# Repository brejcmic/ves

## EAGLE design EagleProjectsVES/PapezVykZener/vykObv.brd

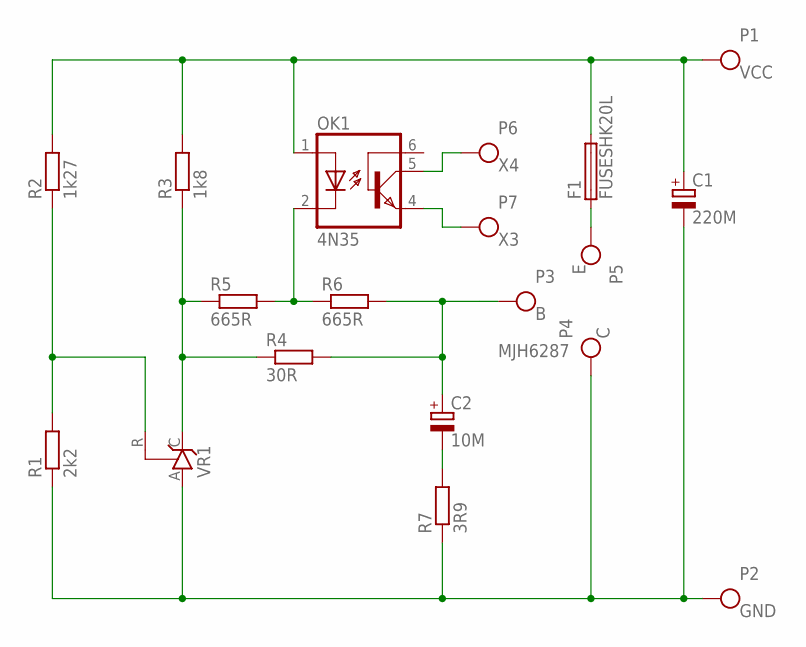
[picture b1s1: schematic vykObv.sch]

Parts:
C1: 220M; E3,5-8
C2: 10M; E22-6
F1: FUSESHK20L; SHK20L
OK1: 4N35; DIL06
P1: VCC; PAD2.5MM
P2: GND; PAD2.5MM
P3: B; PAD2.5MM
P4: C; PAD2.5MM
P5: E; PAD2.5MM
P6: X4; PAD1.6MM
P7: X3; PAD1.6MM
R1: 2k2; 0207/10
R2: 1k27; 0207/10
R3: 1k8; 0207/10
R4: 30R; 0207/10
R5, R6: 665R; 0207/10
R7: 3R9; 0207/10
VR1: TL431CLP; TO92-CLP

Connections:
EMIT: F1.1A (1), F1.1B (1), P5.P$1
GND: C1.-, P2.P$1, P4.P$1, R1.1, R7.1, VR1.A
unnamed: OK1.2 (C), R5.2, R6.1
unnamed: C2.+, P3.P$1, R4.2, R6.2
unnamed: R3.1, R4.1, R5.1, VR1.C
unnamed: OK1.4 (EMI), P7.P$1
unnamed: OK1.5 (COL), P6.P$1
unnamed: R1.2, R2.1, VR1.R
unnamed: C2.-, R7.2
VDD: C1.+, F1.2A (2), F1.2B (2), OK1.1 (A), P1.P$1, R2.2, R3.2

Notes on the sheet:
MJH6287

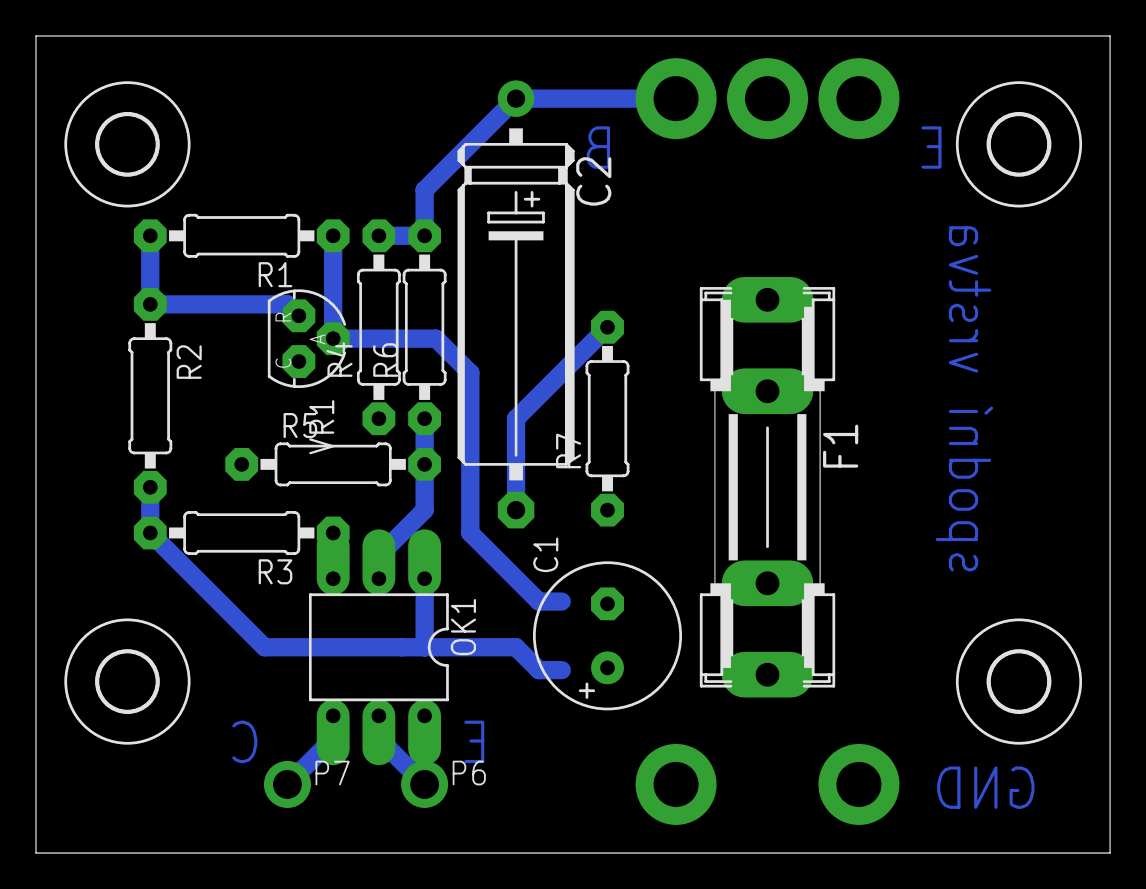
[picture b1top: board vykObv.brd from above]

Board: 2 copper layers, 59.7 x 45.4 mm, 23 parts (0 on the bottom side), 10 nets.

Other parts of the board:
U$1, U$2, U$3, U$4: 3,2

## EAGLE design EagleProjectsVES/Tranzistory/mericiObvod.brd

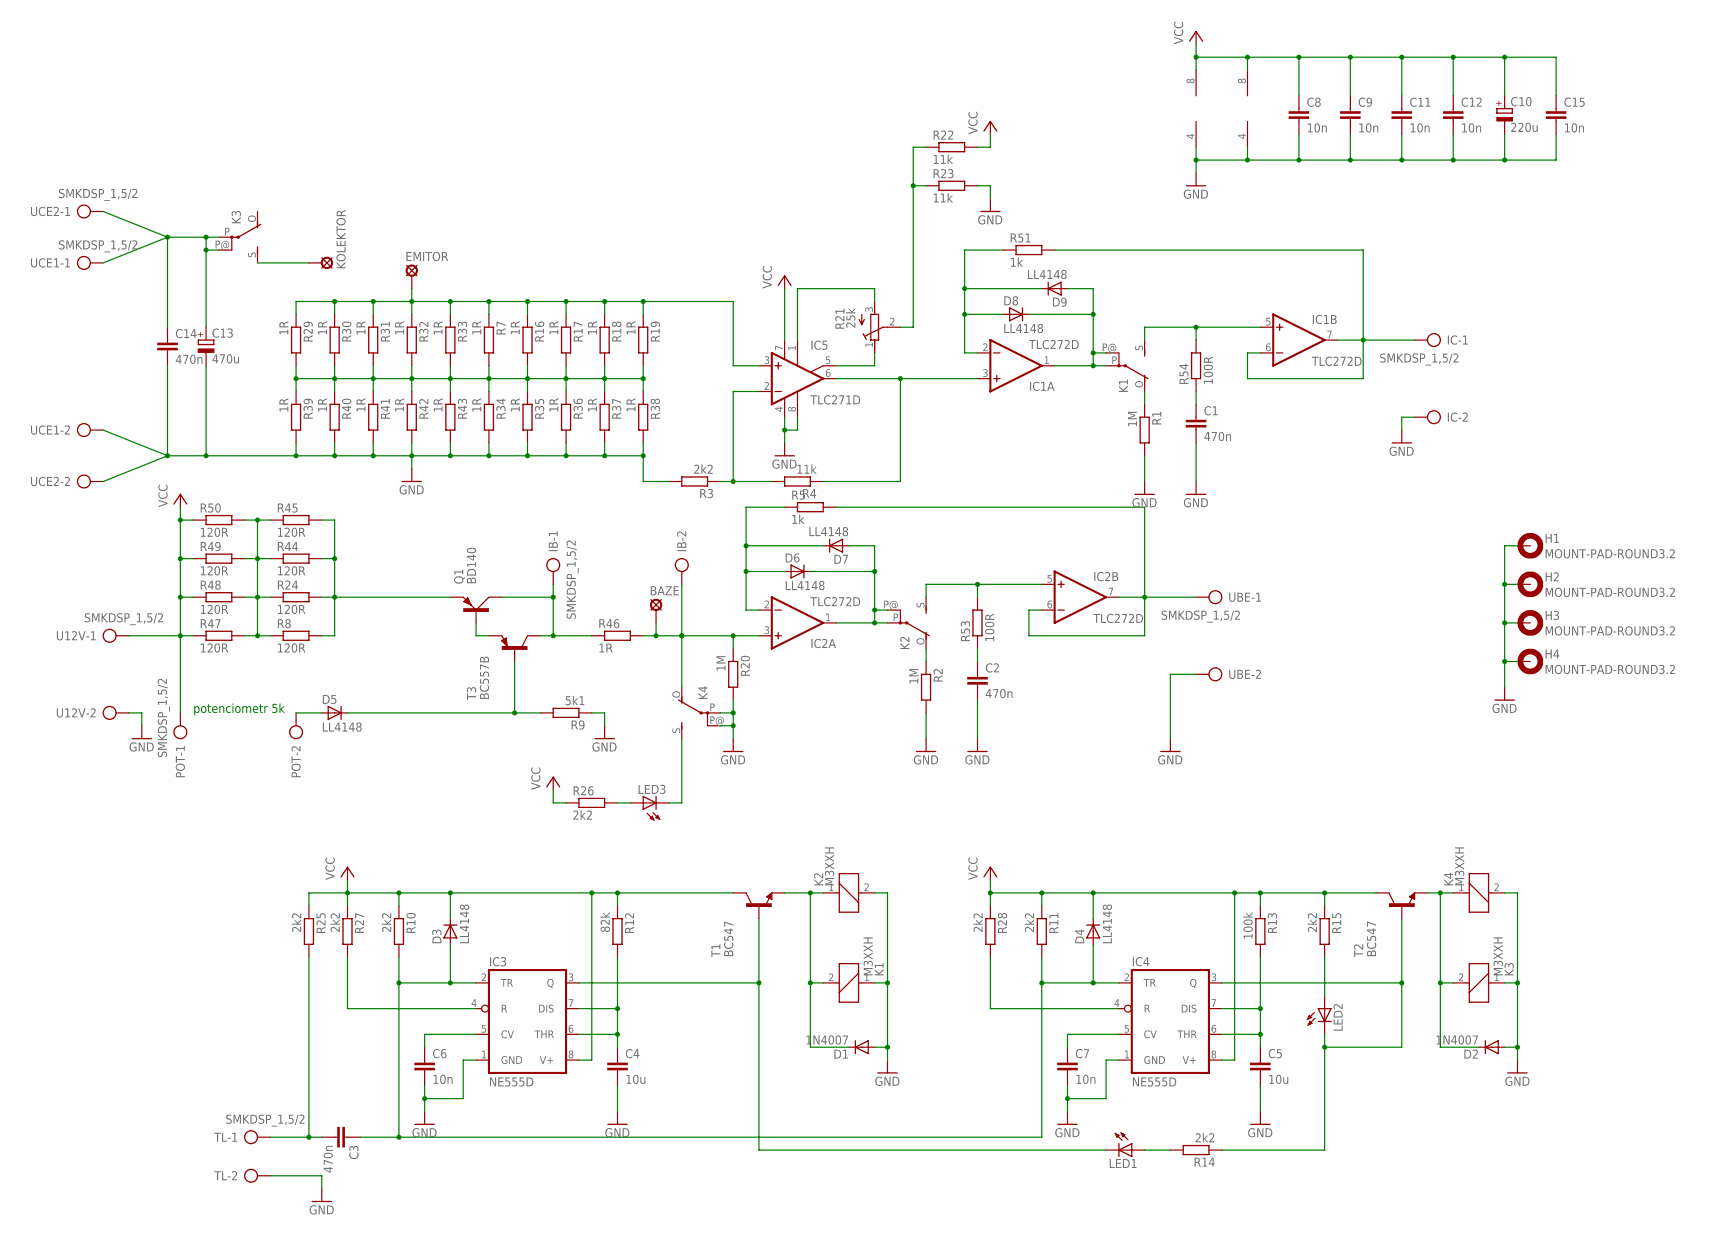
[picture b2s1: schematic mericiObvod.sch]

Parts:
BAZE: SE13
C1, C2, C3: 470n; C0805K
C4, C5: 10u; C0805K
C6, C7, C8, C9, C11, C12, C15: 10n; C0805K
C10: 220u; E5-8,5
C13: 470u; E5-8,5
C14: 470n; C050-030X075
D1, D2: 1N4007; DO41-10
D3, D4, D5, D6, D7, D8, D9: LL4148; SOD80
EMITOR: SE13
H1, H2, H3, H4: MOUNT-PAD-ROUND3.2; 3,2-PAD
IB: SMKDSP_1,5/2
IC: SMKDSP_1,5/2
IC1, IC2: TLC272D; SO08
IC3, IC4: NE555D; SO08
IC5: TLC271D; SO08
K1, K2, K3, K4: M3XXH
KOLEKTOR: SE13
LED1, LED2, LED3: LED3MM
POT: SMKDSP_1,5/2
Q1: BD140; TO126AV
R1, R2, R20: 1M; R0805
R3, R10, R11, R14, R15, R25, R26, R27, R28: 2k2; R0805
R4, R22, R23: 11k; R0805
R5, R51: 1k; R0805
R7, R16, R17, R18, R19, R29, R30, R31, R32, R33, R34, R35, R36, R37, R38, R39, R40, R41, R42, R43, R46: 1R; R0805
R8, R24, R44, R45, R47, R48, R49, R50: 120R; R0805
R9: 5k1; R0805
R12: 82k; R0805
R13: 100k; R0805
R21: 25k; RTRIMT18
R53, R54: 100R; R0805
T1, T2: BC547; TO92-CBE
T3: BC557B; TO92-EBC
TL: SMKDSP_1,5/2
U12V: SMKDSP_1,5/2
UBE: SMKDSP_1,5/2
UCE1, UCE2: SMKDSP_1,5/2

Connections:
GND: C1.2, C2.2, C4.2, C5.2, C6.2, C7.2, C8.2, C9.2, C10.-, C11.2, C12.2, C13.-, C14.2, C15.2, D1.A, D2.A, H1.B3,2, H2.B3,2, H3.B3,2, H4.B3,2, IC.2, IC1.4 (V-), IC2.4 (V-), IC3.1 (GND), IC4.1 (GND), IC5.4 (V-), IC5.8 (OPT), K1.1, K2.2, K3.1, K4.2, K4.P, K4.P@, R1.2, R2.2, R3.2, R9.1, R20.2, R23.2, R34.2, R35.2, R36.2, R37.2, R38.2, R39.2, R40.2, R41.2, R42.2, R43.2, TL.2, U12V.2, UBE.2, UCE1.2, UCE2.2
unnamed: IC5.2 (-IN), R3.1, R4.2
unnamed: IC2.6 (-IN), IC2.7 (OUT), R5.2, UBE.1
unnamed: C1.1, R54.1
unnamed: C2.1, R53.1
unnamed: D6.1 (C), D7.2 (A), IC2.1 (OUT), K2.P, K2.P@
unnamed: D8.1 (C), D9.2 (A), IC1.1 (OUT), K1.P, K1.P@
unnamed: K2.O, R2.1
unnamed: R7.2, R16.2, R17.2, R18.2, R19.2, R29.2, R30.2, R31.2, R32.2, R33.2, R34.1, R35.1, R36.1, R37.1, R38.1, R39.1, R40.1, R41.1, R42.1, R43.1
unnamed: Q1.B, T3.E
unnamed: IC.1, IC1.6 (-IN), IC1.7 (OUT), R51.2
unnamed: D6.2 (A), D7.1 (C), IC2.2 (-IN), R5.1
unnamed: R8.1, R24.1, R44.1, R45.1, R47.2, R48.2, R49.2, R50.2
unnamed: BAZE.MP, IB.2, IC2.3 (+IN), K4.O, R20.1, R46.2
unnamed: D5.2 (A), POT.2
unnamed: D5.1 (C), R9.2, T3.B
unnamed: IB.1, Q1.C, R46.1, T3.C
unnamed: Q1.E, R8.2, R24.2, R44.2, R45.2
unnamed: D1.C, K1.2, K2.1, T1.E
unnamed: IC3.3 (Q), LED1.K (C), T1.B
unnamed: IC4.3 (Q), LED2.K (C), R14.1, T2.B
unnamed: D2.C, K3.2, K4.1, T2.E
unnamed: C3.1, D3.2 (A), D4.2 (A), IC3.2 (TR), IC4.2 (TR), R10.2, R11.2
unnamed: LED1.A, R14.2
unnamed: C5.1, IC4.6 (THR), IC4.7 (DIS), R13.2
unnamed: C4.1, IC3.6 (THR), IC3.7 (DIS), R12.2
unnamed: C6.1, IC3.5 (CV)
unnamed: IC1.3 (+IN), IC5.6 (OUT), R4.1
unnamed: C7.1, IC4.5 (CV)
unnamed: LED2.A, R15.2
unnamed: C3.2, R25.2, TL.1
unnamed: LED3.A, R26.2
unnamed: IC5.5 (ON2), R21.1 (E)
unnamed: IC5.1 (ON1), R21.3 (A)
unnamed: R21.2 (S), R22.1, R23.1
unnamed: K4.S, LED3.K (C)
unnamed: IC3.4 (R), R27.2
unnamed: IC4.4 (R), R28.2
unnamed: K1.O, R1.1
unnamed: D8.2 (A), D9.1 (C), IC1.2 (-IN), R51.1
unnamed: C13.+, C14.1, K3.P, K3.P@, UCE1.1, UCE2.1
unnamed: IC1.5 (+IN), K1.S, R54.2
unnamed: IC2.5 (+IN), K2.S, R53.2
unnamed: EMITOR.MP, IC5.3 (+IN), R7.1, R16.1, R17.1, R18.1, R19.1, R29.1, R30.1, R31.1, R32.1, R33.1
unnamed: K3.S, KOLEKTOR.MP
VCC: C8.1, C9.1, C10.+, C11.1, C12.1, C15.1, D3.1 (C), D4.1 (C), IC1.8 (V+), IC2.8 (V+), IC3.8 (V+), IC4.8 (V+), IC5.7 (V+), POT.1, R10.1, R11.1, R12.1, R13.1, R15.1, R22.2, R25.1, R26.1, R27.1, R28.1, R47.1, R48.1, R49.1, R50.1, T1.C, T2.C, U12V.1

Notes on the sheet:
potenciometr 5k

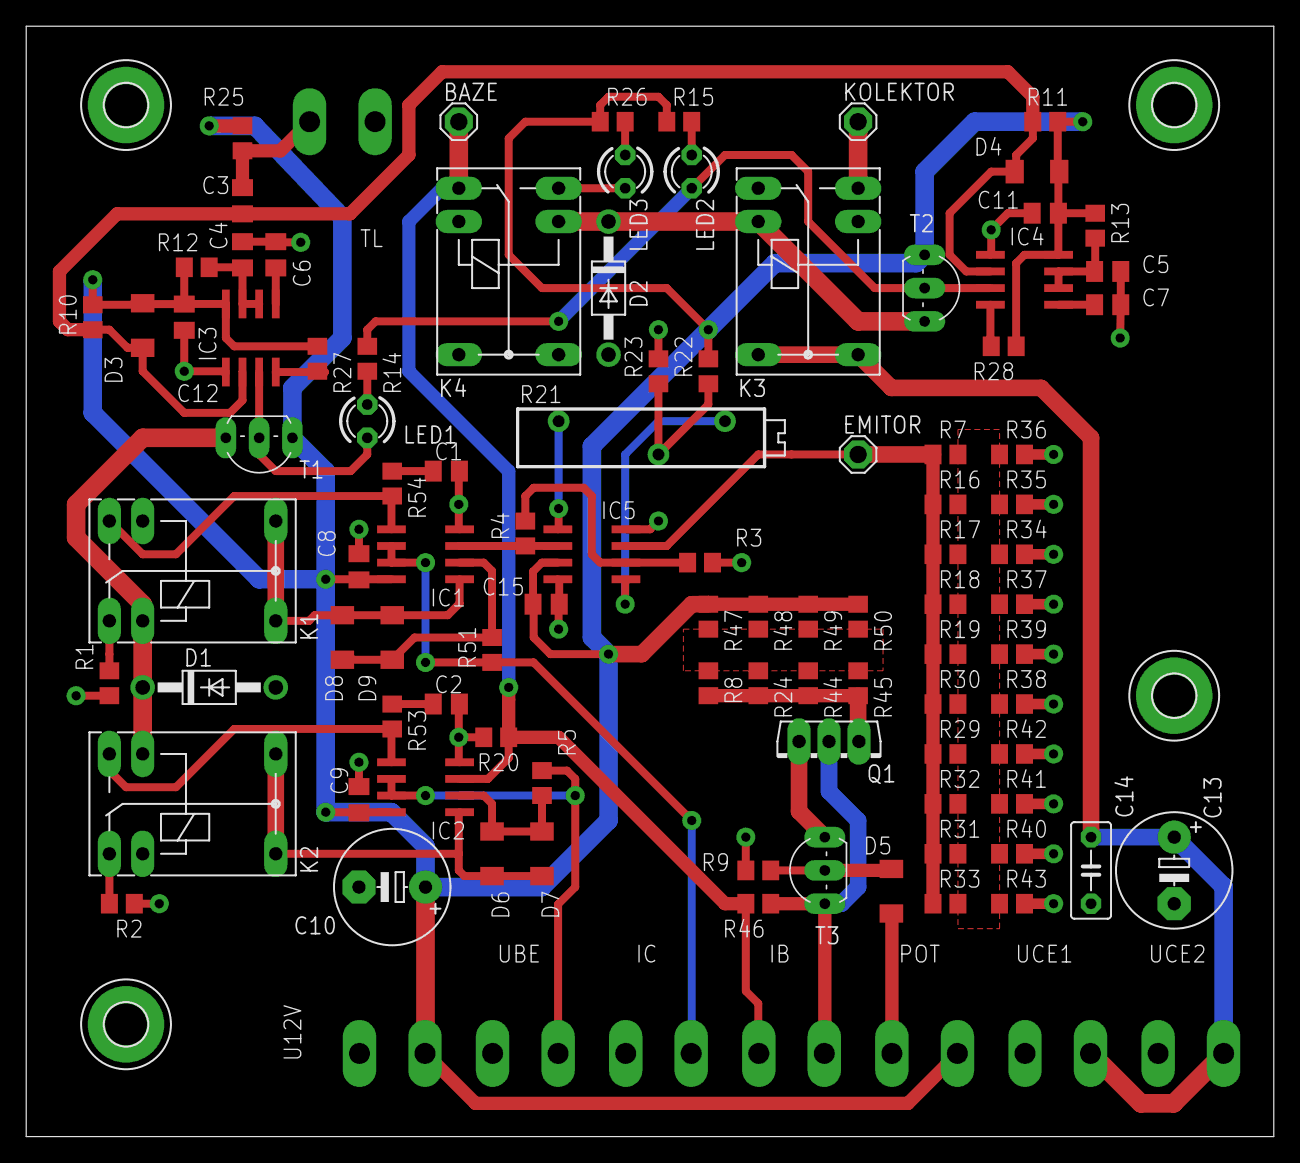
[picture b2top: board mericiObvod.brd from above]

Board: 2 copper layers, 95.2 x 84.8 mm, 107 parts (0 on the bottom side), 46 nets.

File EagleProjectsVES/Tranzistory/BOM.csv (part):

Partlist exported from C:/Users/brejcmic/GITs/ves/EagleProjectsVES/Tranzistory/mericiObvod.sch at 19.9.2017 11:37:58

Qty Value              Device              Package      Parts                                                                                                  Description                                                               MF      MPN     OC_FARNELL OC_NEWARK
2                      BC547B-NPN-TO92-CBE TO92-CBE     T1, T2                                                                                                 NPN Transistror                                                                                               
3                      LED3MM              LED3MM       LED1, LED2, LED3                                                                                       LED                                                                                                           
2   100R               R-EU_R0805          R0805        R53, R54                                                                                               RESISTOR, European symbol                                                                                     
1   100k               R-EU_R0805          R0805        R13                                                                                                    RESISTOR, European symbol                                                                                     
7   10n                C-EUC0805K          C0805K       C6, C7, C8, C9, C11, C12, C15                                                                          CAPACITOR, European symbol                                                                                    
2   10u                C-EUC0805K          C0805K       C4, C5                                                                                                 CAPACITOR, European symbol                                                                                    
3   11k                R-EU_R0805          R0805        R4, R22, R23                                                                                           RESISTOR, European symbol                                                                                     
8   120R               R-EU_R0805          R0805        R8, R24, R44, R45, R47, R48, R49, R50                                                                  RESISTOR, European symbol                                                                                     
3   1M                 R-EU_R0805          R0805        R1, R2, R20                                                                                            RESISTOR, European symbol                                                                                     
2   1N4007             DIODE-DO41-10       DO41-10      D1, D2                                                                                                 DIODE                                                                                                         
21  1R                 R-EU_R0805          R0805        R7, R16, R17, R18, R19, R29, R30, R31, R32, R33, R34, R35, R36, R37, R38, R39, R40, R41, R42, R43, R46 RESISTOR, European symbol                                                                                     
2   1k                 R-EU_R0805          R0805        R5, R51                                                                                                RESISTOR, European symbol                                                                                     
1   220u               CPOL-EUE5-8.5       E5-8,5       C10                                                                                                    POLARIZED CAPACITOR, European symbol                                                                          
1   25k                R-TRIMMT18          RTRIMT18     R21                                                                                                    Trimm resistor                                                                                                
9   2k2                R-EU_R0805          R0805        R3, R10, R11, R14, R15, R25, R26, R27, R28                                                             RESISTOR, European symbol                                                                                     
1   470n               C-EU050-030X075     C050-030X075 C14                                                                                                    CAPACITOR, European symbol                                                                                    
3   470n               C-EUC0805K          C0805K       C1, C2, C3                                                                                             CAPACITOR, European symbol                                                                                    
1   470u               CPOL-EUE5-8.5       E5-8,5       C13                                                                                                    POLARIZED CAPACITOR, European symbol                                                                          
1   5k1                R-EU_R0805          R0805        R9                                                                                                     RESISTOR, European symbol                                                                                     
1   82k                R-EU_R0805          R0805        R12                                                                                                    RESISTOR, European symbol                                                                                     
1   BC557B             BC557B              TO92-EBC     T3                                                                                                     PNP Transistror                                                                                               
1   BD140              BD140               TO126AV      Q1                                                                                                     PNP TRANSISTOR                                                                                                
7   LL4148             D-SOD-80            SOD80        D3, D4, D5, D6, D7, D8, D9                                                                             DIODE                                                                                                         
4   M3XXH              M3XXH               M3XXH        K1, K2, K3, K4                                                                                         RELAY                                                                                     unknown    unknown  
4   MOUNT-PAD-ROUND3.2 MOUNT-PAD-ROUND3.2  3,2-PAD      H1, H2, H3, H4                                                                                         MOUNTING PAD, round                                                                                           
2   NE555D             NE555D              SO08         IC3, IC4                                                                                               TIMER                                                                                                         
3   SE13               SE13                SE13         BAZE, EMITOR, KOLEKTOR                                                                                 SOLDER PAD E1542,  drill 1,3mm, distributor Buerklin, 07F815                                                  
8   SMKDSP_1,5/2       SMKDSP_1,5/2        SMKDSP_1,5/2 IB, IC, POT, TL, U12V, UBE, UCE1, UCE2                                                                 Printklemme, Nennstrom: 17,5 A, Bemessungsspannung: 250 V, Raster: 5,0 mm FARNELL 1733570 3041244    69C8588  
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
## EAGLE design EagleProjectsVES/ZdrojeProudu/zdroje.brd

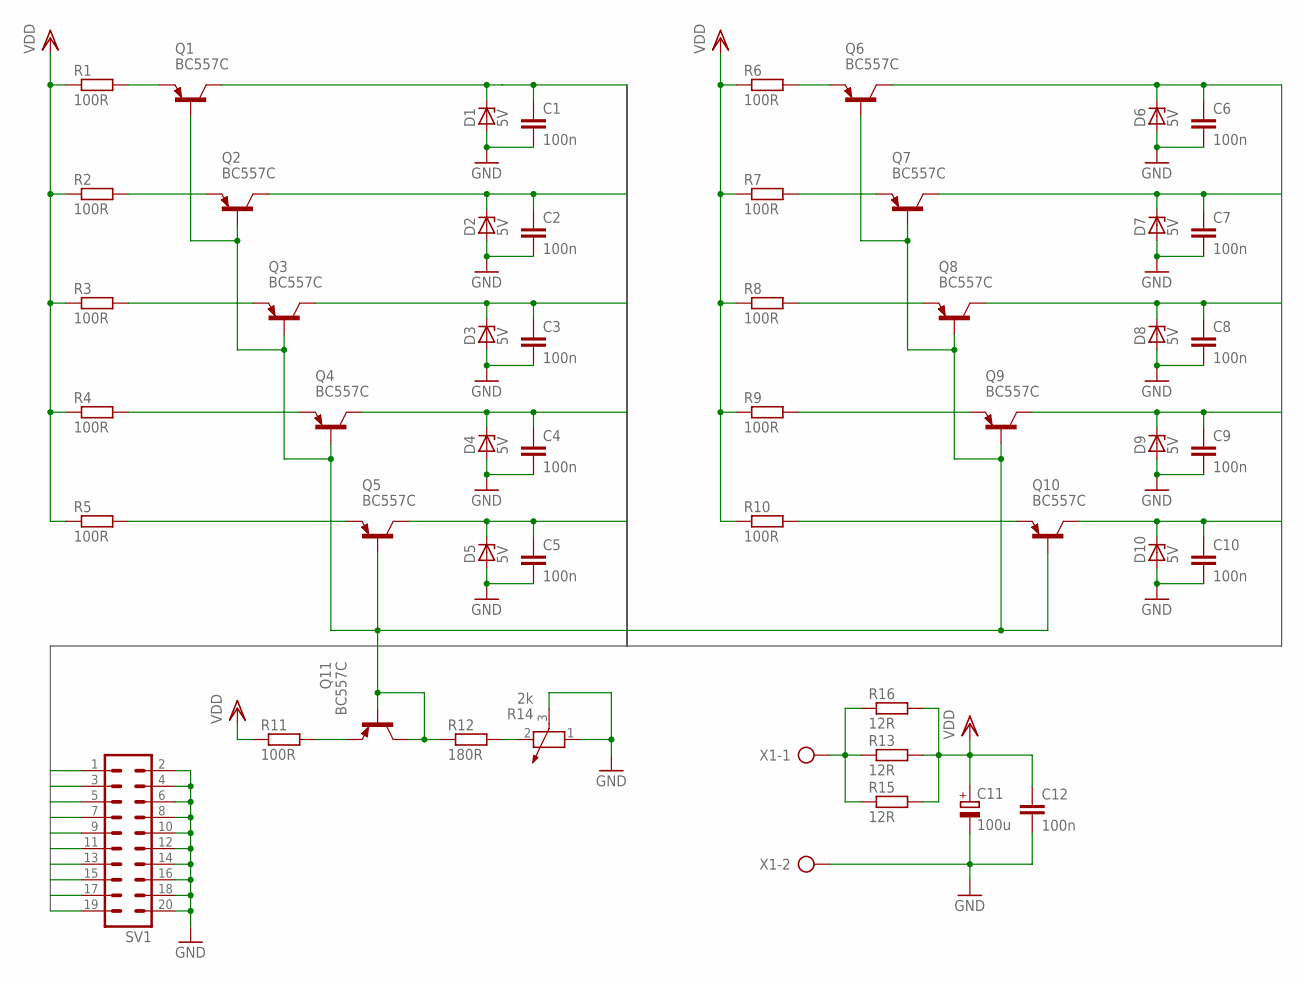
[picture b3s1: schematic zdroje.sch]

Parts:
C1, C2, C3, C4, C5, C6, C7, C8, C9, C10, C12: 100n; C050-030X075
C11: 100u; E5-8,5
D1, D2, D3, D4, D5, D6, D7, D8, D9, D10: 5V; DO35Z10
Q1, Q2, Q3, Q4, Q5, Q6, Q7, Q8, Q9, Q10, Q11: BC557C; TO92-EBC
R1, R2, R3, R4, R5, R6, R7, R8, R9, R10, R11: 100R; 0207/10
R12: 180R; 0207/10
R13, R15, R16: 12R; 0207/10
R14: 2k; PT-SPIN
SV1: MA10-2
X1: AK300/2

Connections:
GND: C1.2, C2.2, C3.2, C4.2, C5.2, C6.2, C7.2, C8.2, C9.2, C10.2, C11.-, C12.2, D1.A, D2.A, D3.A, D4.A, D5.A, D6.A, D7.A, D8.A, D9.A, D10.A, R14.1, R14.3, SV1.2, SV1.4, SV1.6, SV1.8, SV1.10, SV1.12, SV1.14, SV1.16, SV1.18, SV1.20, X1.2
I1: C1.1, D1.C, Q1.C, SV1.1
I2: C2.1, D2.C, Q2.C, SV1.3
I3: C3.1, D3.C, Q3.C, SV1.5
I4: C4.1, D4.C, Q4.C, SV1.7
I5: C5.1, D5.C, Q5.C, SV1.9
I6: C6.1, D6.C, Q6.C, SV1.11
I7: C7.1, D7.C, Q7.C, SV1.13
I8: C8.1, D8.C, Q8.C, SV1.15
I9: C9.1, D9.C, Q9.C, SV1.17
I10: C10.1, D10.C, Q10.C, SV1.19
unnamed: Q1.E, R1.2
unnamed: Q2.E, R2.2
unnamed: Q3.E, R3.2
unnamed: Q4.E, R4.2
unnamed: Q5.E, R5.2
unnamed: Q6.E, R6.2
unnamed: Q7.E, R7.2
unnamed: Q8.E, R8.2
unnamed: Q9.E, R9.2
unnamed: Q10.E, R10.2
unnamed: R12.2, R14.2
unnamed: Q1.B, Q2.B, Q3.B, Q4.B, Q5.B, Q6.B, Q7.B, Q8.B, Q9.B, Q10.B, Q11.B, Q11.C, R12.1
unnamed: Q11.E, R11.2
unnamed: R13.1, R15.1, R16.1, X1.1
VDD: C11.+, C12.1, R1.1, R2.1, R3.1, R4.1, R5.1, R6.1, R7.1, R8.1, R9.1, R10.1, R11.1, R13.2, R15.2, R16.2

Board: 2 copper layers, 51 parts (0 on the bottom side), 26 nets, no tracks yet.

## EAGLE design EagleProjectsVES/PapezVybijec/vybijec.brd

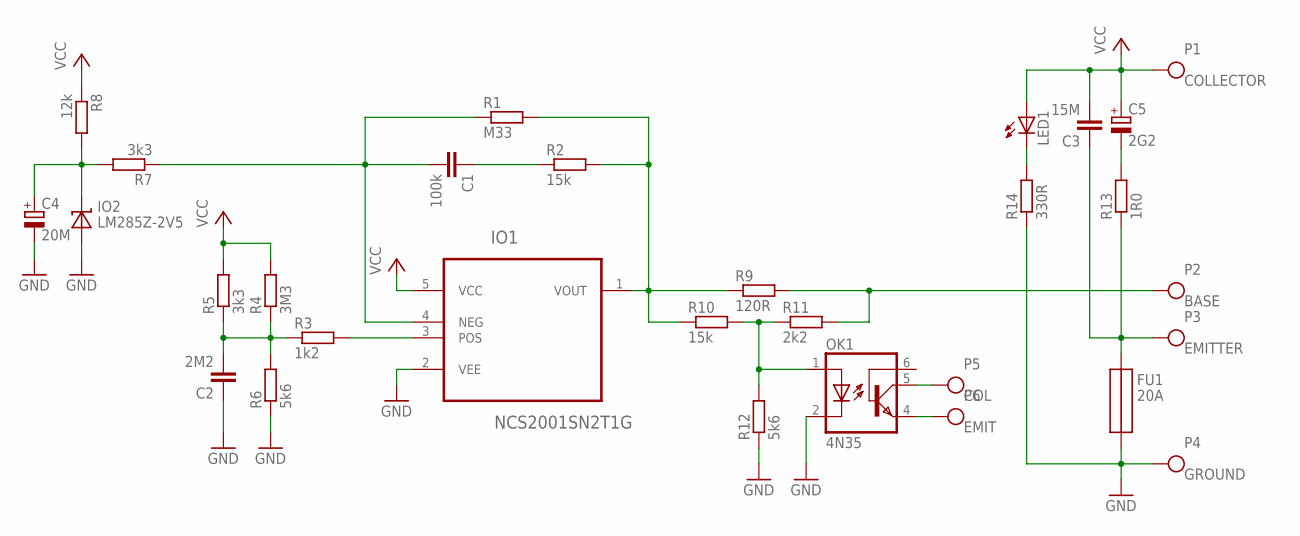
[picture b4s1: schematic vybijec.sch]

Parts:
C1: 100k; C050-025X075
C2: 2M2; C050-050X075
C3: 15M; C050-075X075
C4: 20M; E22-6
C5: 2G2; E5-10,5
FU1: 20A; POJ20X6
IO1: NCS2001SN2T1G; SOT95P275X110-5N
IO2: LM285Z-2V5; TO92-
LED1: LED3MM
OK1: 4N35; DIL06
P1: COLLECTOR; PAD3MM
P2: BASE; PAD3MM
P3: EMITTER; PAD3MM
P4: GROUND; PAD3MM
P5: COL; PAD1.6MM
P6: EMIT; PAD1.6MM
R1: M33; 0207/10
R2, R10: 15k; 0207/10
R3: 1k2; 0207/10
R4: 3M3; 0207/10
R5, R7: 3k3; 0207/10
R6, R12: 5k6; 0207/10
R8: 12k; 0207/10
R9: 120R; 0207/10
R11: 2k2; 0207/10
R13: 1R0; R1206
R14: 330R; 0207/10

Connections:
GND: C2.1, C4.-, FU1.2-1, FU1.2-2, FU1.2-3, FU1.2-4, IO1.2 (VEE), IO2.1 (ANODE), OK1.2 (C), P4.1, R6.1, R12.1, R14.1
unnamed: C1.1, R2.1
unnamed: IO1.1 (VOUT), R1.2, R2.2, R9.1, R10.1
unnamed: C4.+, IO2.2 (KATODE), R7.2, R8.2
unnamed: C1.2, IO1.4 (NEG), R1.1, R7.1
unnamed: IO1.3 (POS), R3.2
unnamed: C2.2, R3.1, R4.1, R5.1, R6.2
unnamed: C3.1, FU1.1-1, FU1.1-2, FU1.1-3, FU1.1-4, P3.1, R13.1
unnamed: OK1.1 (A), R10.2, R11.1, R12.2
unnamed: P2.1, R9.2, R11.2
unnamed: OK1.5 (COL), P5.P$1
unnamed: OK1.4 (EMI), P6.P$1
unnamed: LED1.K (C), R14.2
unnamed: C5.-, R13.2
VCC: C3.2, C5.+, IO1.5 (VCC), LED1.A, P1.1, R4.2, R5.2, R8.1

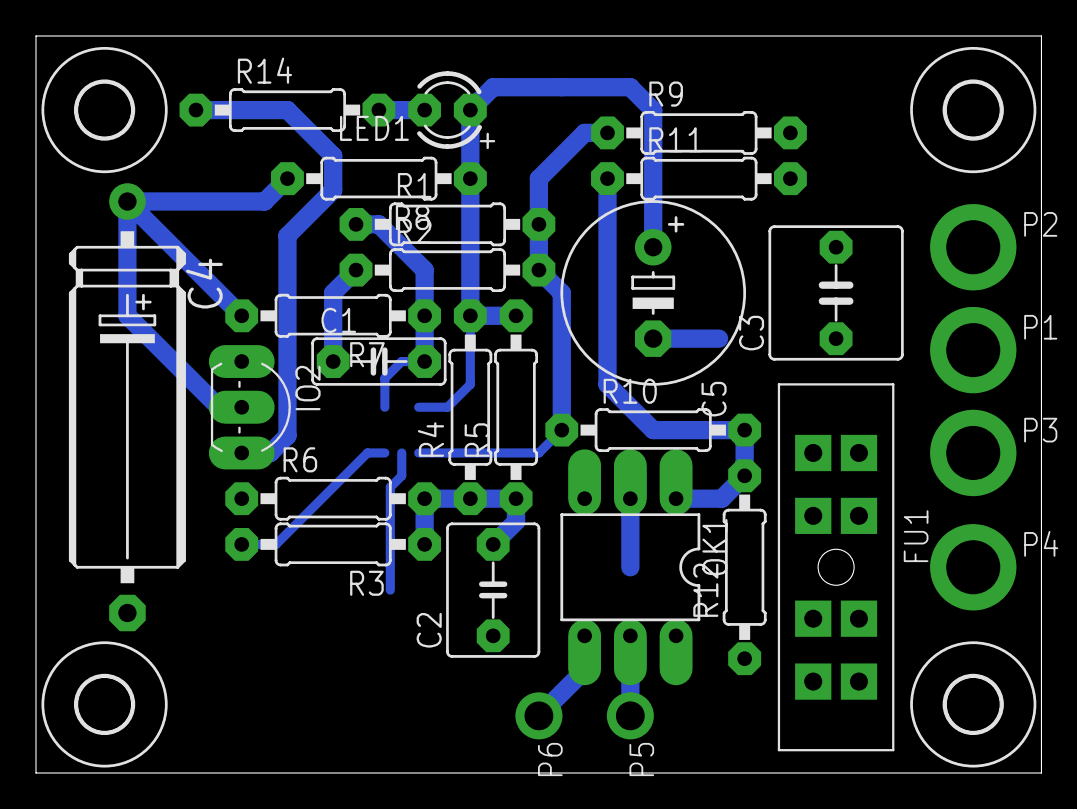
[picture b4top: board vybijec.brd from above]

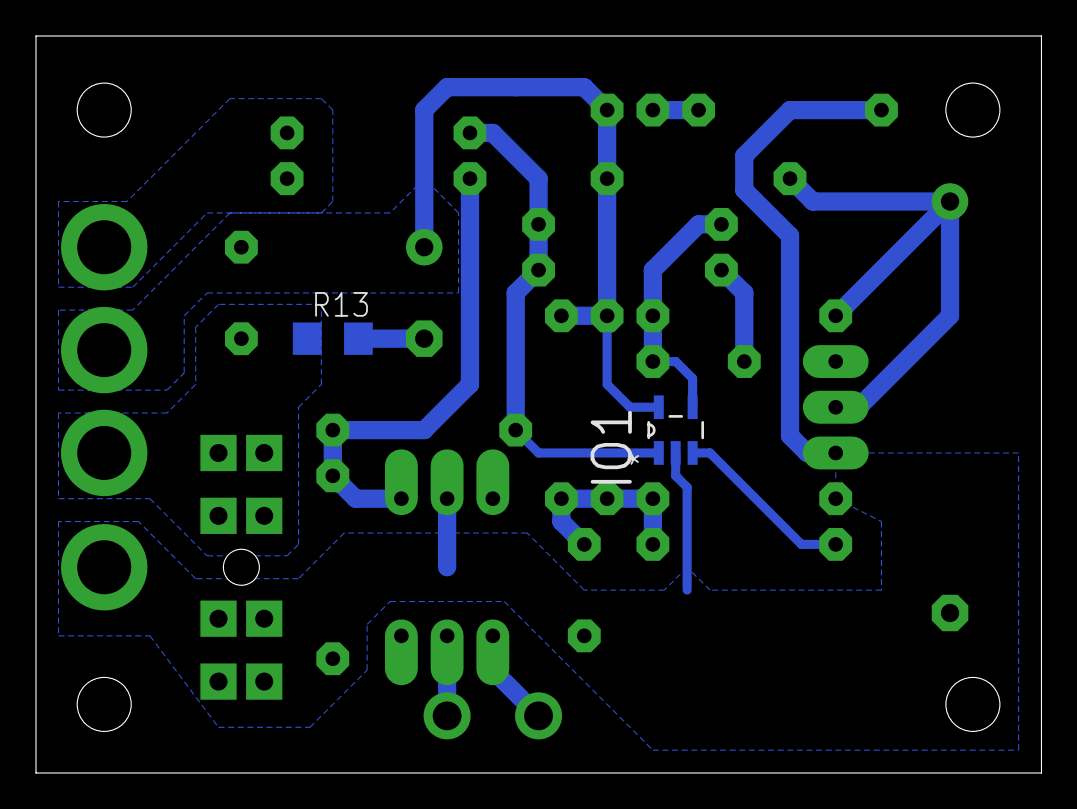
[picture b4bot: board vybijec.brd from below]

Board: 2 copper layers, 55.9 x 40.9 mm, 34 parts (2 on the bottom side), 15 nets.

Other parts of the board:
U$1, U$2, U$3, U$4: 3,0

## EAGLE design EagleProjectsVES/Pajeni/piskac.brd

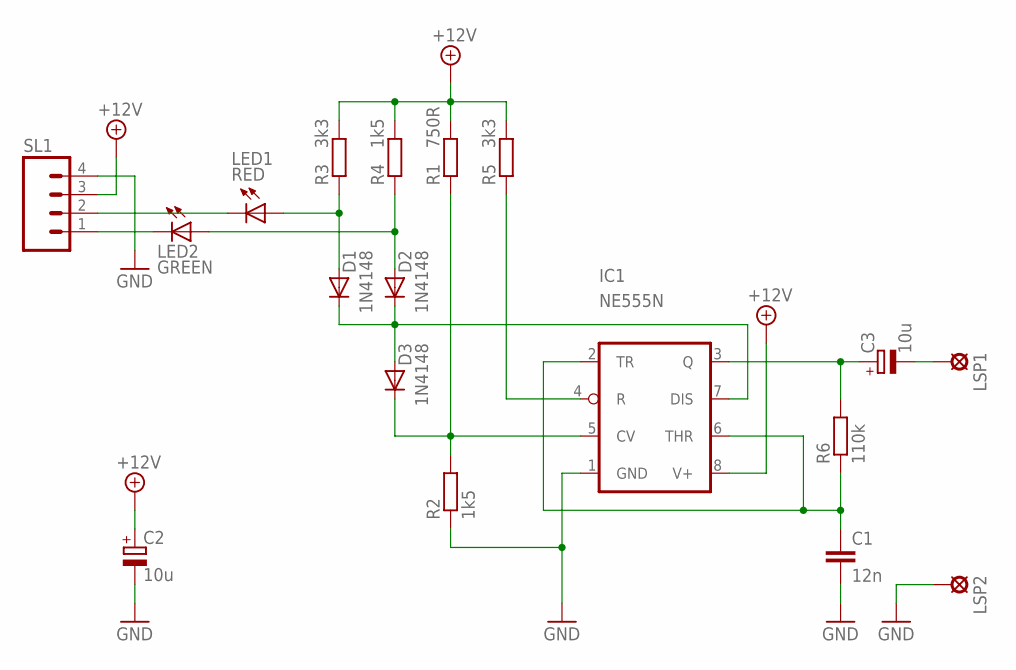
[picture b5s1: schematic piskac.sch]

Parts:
C1: 12n; C5B3.5
C2, C3: 10u; E2,5-6
D1, D2, D3: 1N4148; DO35-10
IC1: NE555N; DIL08
LED1: RED; LED3MM
LED2: GREEN; LED3MM
LSP1, LSP2: LSP10
R1: 750R; 0207/10
R2, R4: 1k5; 0207/10
R3, R5: 3k3; 0207/10
R6: 110k; 0207/10
SL1: M04; 04P

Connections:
+12V: C2.+, IC1.8 (V+), R1.2, R3.2, R4.2, R5.2, SL1.3
GND: C1.2, C2.-, IC1.1 (GND), LSP2.MP, R2.1, SL1.4
unnamed: C1.1, IC1.2 (TR), IC1.6 (THR), R6.1
unnamed: D3.C, IC1.5 (CV), R1.1, R2.2
unnamed: C3.-, LSP1.MP
unnamed: IC1.4 (R), R5.1
unnamed: D1.A, LED1.A, R3.1
unnamed: LED1.K (C), SL1.2
unnamed: D2.A, LED2.A, R4.1
unnamed: C3.+, IC1.3 (Q), R6.2
unnamed: D1.C, D2.C, D3.A, IC1.7 (DIS)
unnamed: LED2.K (C), SL1.1

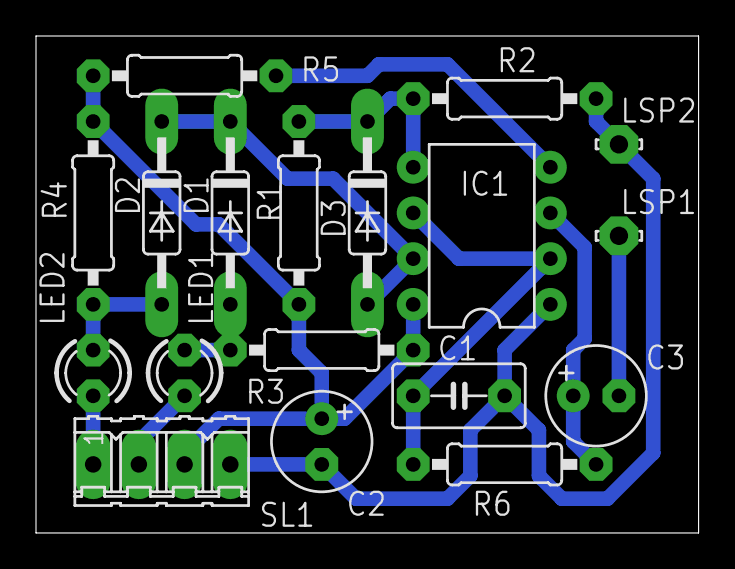
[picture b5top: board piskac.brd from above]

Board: 2 copper layers, 36.8 x 27.6 mm, 18 parts (0 on the bottom side), 12 nets.
